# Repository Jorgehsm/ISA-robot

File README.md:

# ISA robot
Carro robô baseado em esp32 controlado por controle bluetooth.

O projeto utiliza Bluepad32 na comunicação entre o controle e o esp32. Para mais informações acesse: <https://bluepad32.readthedocs.io/en/latest/plat_arduino/>

Desenvolvido utilizando Platform.io.

Breakout board para conexão do esp32 com os diversos sensores e componentes utilizados desenvolvida utilizando KiCad.

Modelagem do chassi para fabricação em impressão 3D desenvolvida utilizando SolidWorks.

Projeto pessoal em desenvolvimento.

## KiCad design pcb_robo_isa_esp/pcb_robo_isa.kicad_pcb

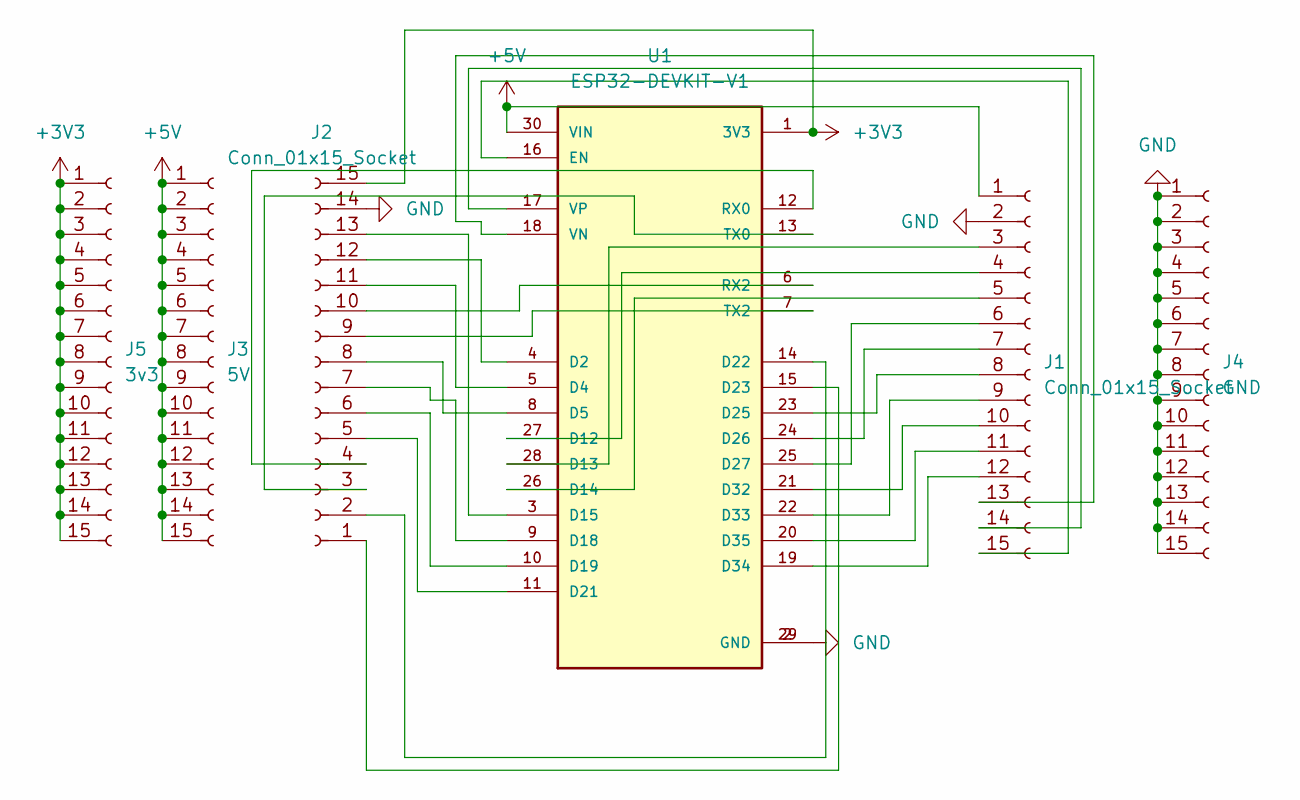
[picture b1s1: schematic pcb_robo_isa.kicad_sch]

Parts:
J1, J2: Conn_01x15_Socket; PinHeader_1x15_P2.54mm_Vertical
J3: 5V; PinHeader_1x15_P2.54mm_Vertical
J4: GND; PinHeader_1x15_P2.54mm_Vertical
J5: 3v3; PinHeader_1x15_P2.54mm_Vertical
U1: ESP32-DEVKIT-V1; MODULE_ESP32_DEVKIT_V1; PARTREV N/A

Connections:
+3V3: J2.15, J5.1, J5.2, J5.3, J5.4, J5.5, J5.6, J5.7, J5.8, J5.9, J5.10, J5.11, J5.12, J5.13, J5.14, J5.15, U1.1 (3V3)
+5V: J1.1, J3.1, J3.2, J3.3, J3.4, J3.5, J3.6, J3.7, J3.8, J3.9, J3.10, J3.11, J3.12, J3.13, J3.14, J3.15, U1.30 (VIN)
GND: J1.2, J2.14, J4.1, J4.2, J4.3, J4.4, J4.5, J4.6, J4.7, J4.8, J4.9, J4.10, J4.11, J4.12, J4.13, J4.14, J4.15, U1.2 (GND), U1.29 (GND)
unnamed: J1.3, U1.28 (D13)
unnamed: J1.4, U1.27 (D12)
unnamed: J1.5, U1.26 (D14)
unnamed: J1.6, U1.25 (D27)
unnamed: J1.7, U1.24 (D26)
unnamed: J1.8, U1.23 (D25)
unnamed: J1.9, U1.22 (D33)
unnamed: J1.10, U1.21 (D32)
unnamed: J1.11, U1.20 (D35)
unnamed: J1.12, U1.19 (D34)
unnamed: J1.13, U1.18 (VN)
unnamed: J1.14, U1.17 (VP)
unnamed: J1.15, U1.16 (EN)
unnamed: J2.1, U1.15 (D23)
unnamed: J2.2, U1.14 (D22)
unnamed: J2.3, U1.13 (TX0)
unnamed: J2.4, U1.12 (RX0)
unnamed: J2.5, U1.11 (D21)
unnamed: J2.6, U1.10 (D19)
unnamed: J2.7, U1.9 (D18)
unnamed: J2.8, U1.8 (D5)
unnamed: J2.9, U1.7 (TX2)
unnamed: J2.10, U1.6 (RX2)
unnamed: J2.11, U1.5 (D4)
unnamed: J2.12, U1.4 (D2)
unnamed: J2.13, U1.3 (D15)

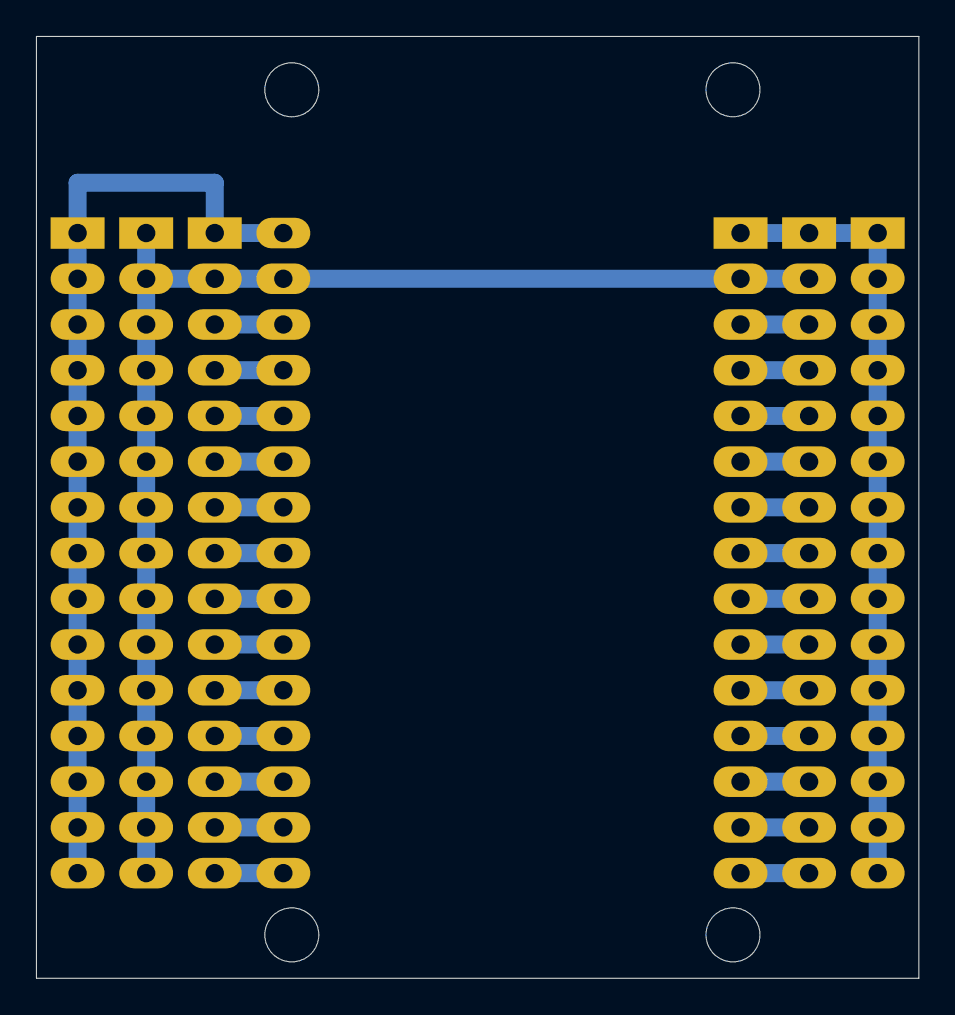
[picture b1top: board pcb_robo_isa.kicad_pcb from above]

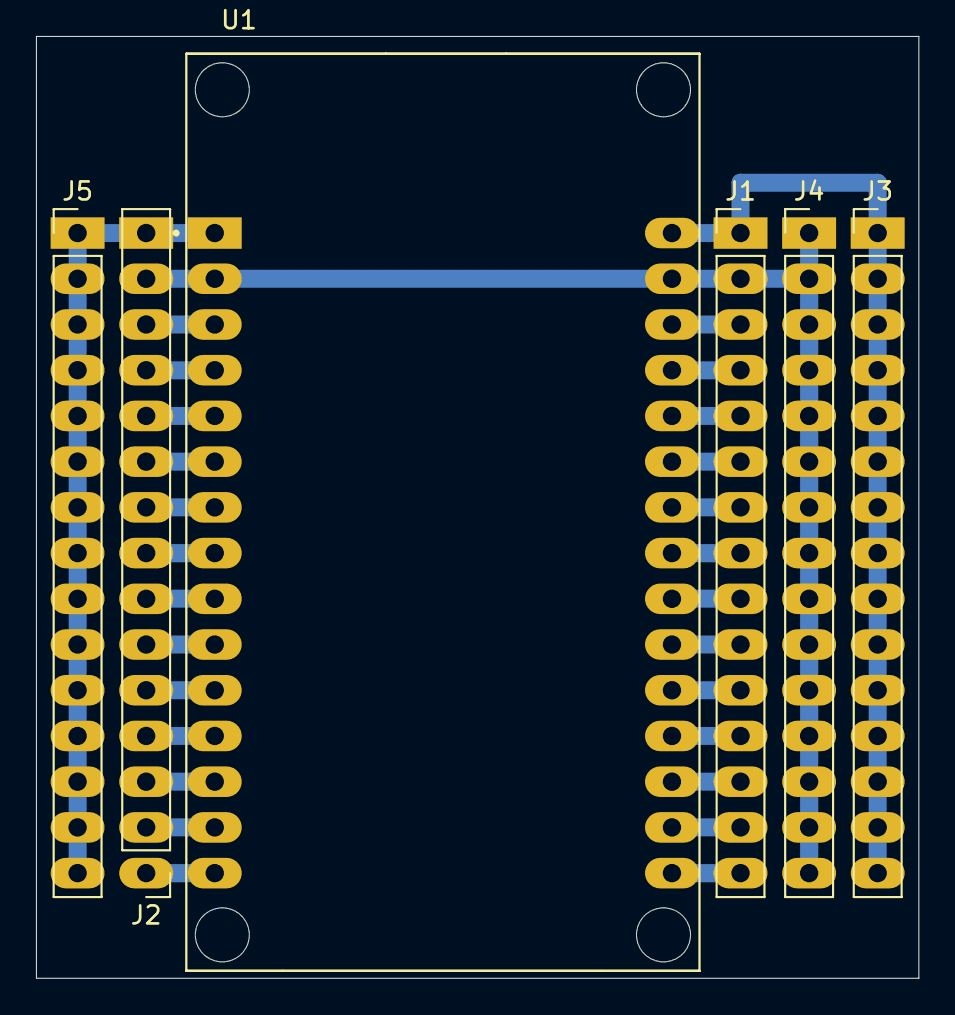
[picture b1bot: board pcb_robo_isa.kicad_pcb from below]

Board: 2 copper layers, 49.0 x 52.3 mm, 6 parts (6 on the bottom side), 29 nets.

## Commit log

2024-09-12 Add files via upload
    código atual do projeto
2024-09-21 Implementação Bluepad32
2024-09-21 Adição do modelo 3D e projeto da PCB
2024-09-21 PinOut de conexão dos componentes no esp32
